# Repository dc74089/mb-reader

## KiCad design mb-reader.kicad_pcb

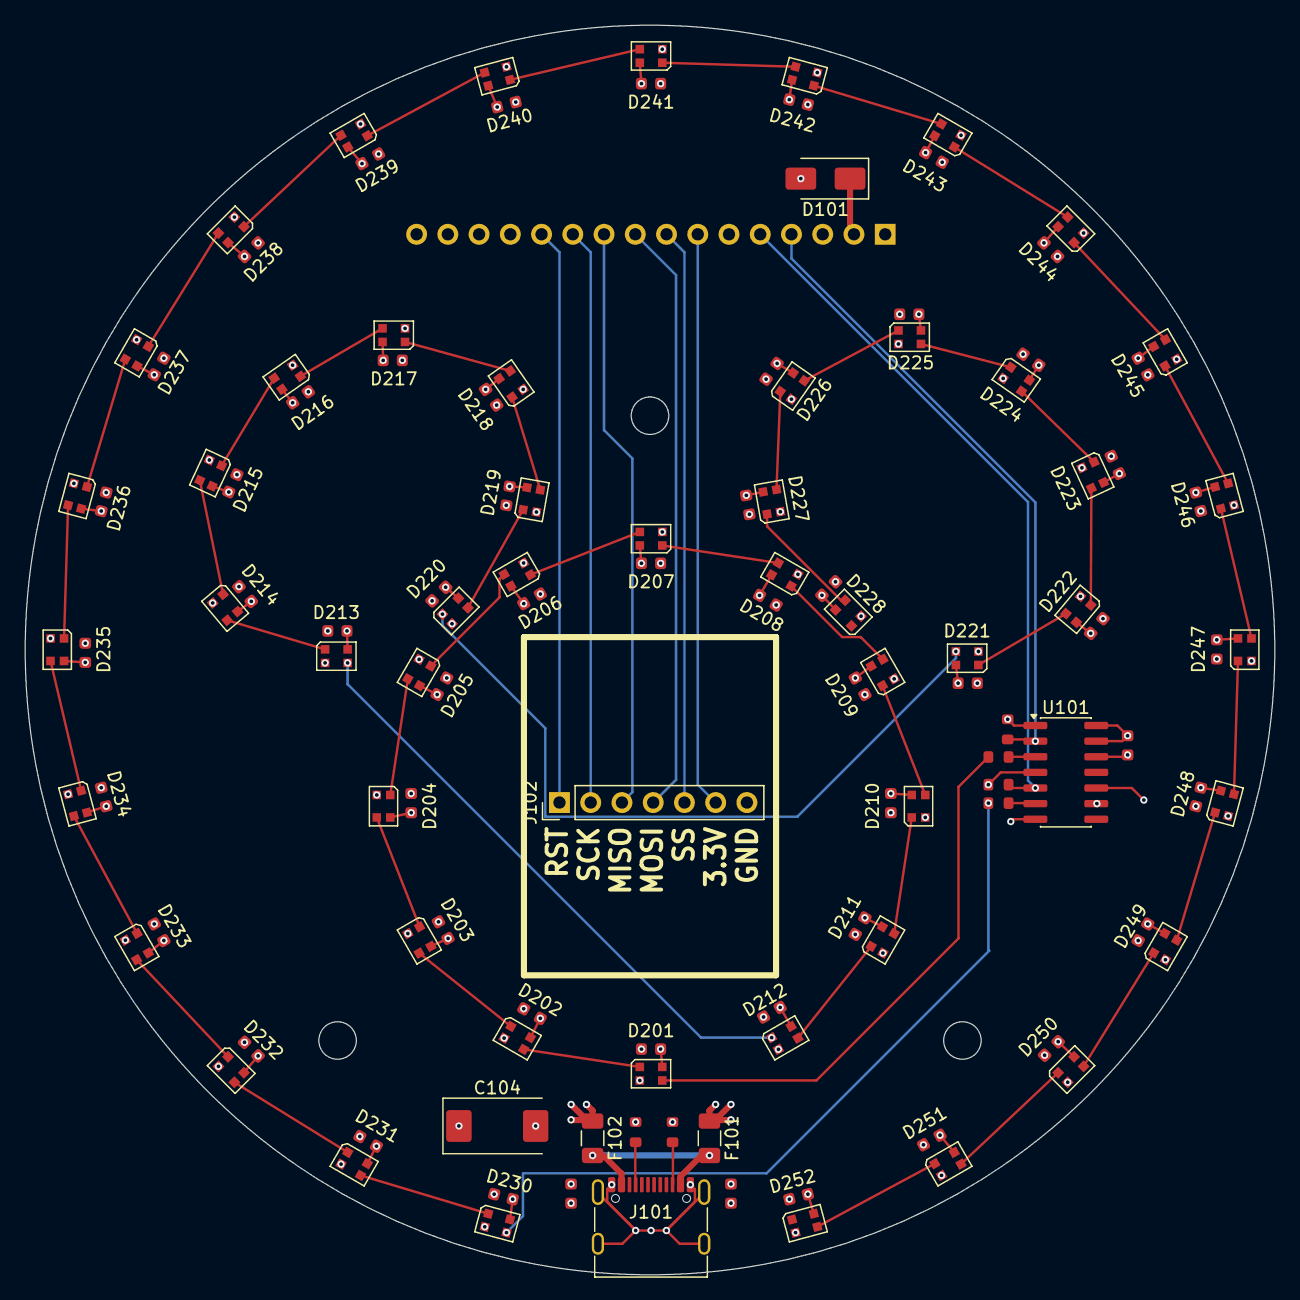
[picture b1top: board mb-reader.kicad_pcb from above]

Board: 4 copper layers, 101.6 x 101.6 mm, 119 parts (1 on the bottom side), 67 nets.

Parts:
C101, C103, C202, C203, C204, C205, C206, C207, C208, C209, C210, C211, C212, C213, C214, C215, C216, C217, C218, C219, C220, C221, C222, C223, C224, C225, C226, C227, C228, C229, C230, C231, C232, C233, C234, C235, C236, C237, C238, C239, C240, C241, C242, C243, C244, C245, C246, C247, C248, C249, C250, C251, C252: 100n; C_0603
C102: 10u; C_0603
C104: 100u; CP_EIA-7343-20_Kemet-V
D101: D; D_SMA
D201, D202, D203, D204, D205, D206, D207, D208, D209, D210, D211, D212, D213, D214, D215, D216, D217, D218, D219, D220, D221, D222, D223, D224, D225, D226, D227, D228, D230, D231, D232, D233, D234, D235, D236, D237, D238, D239, D240, D241, D242, D243, D244, D245, D246, D247, D248, D249, D250, D251, D252: WS2812B-2020; LED_WS2812B-2020_PLCC4_2.0x2.0mm
F101, F102: Polyfuse; Fuse_1206_3216Metric
J101: USB_C_Receptacle_USB2.0_14P; USB_C_Receptacle_G-Switch_GT-USB-7010ASV
J102: Conn_01x07_Socket; PinHeader_1x07_P2.54mm_Vertical
J103: Conn_01x16_Socket; PinHeader_1x16_P2.54mm_Vertical
R101, R102: 5k1; R_0603
R103, R104: 100; R_0603
R106, R107: 10k; R_0603
U101: 74AHCT125; SOIC-14_3.9x8.7mm_P1.27mm

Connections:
+3V3: J102.6, J103.7
+5V: C101.2, C102.2, C103.2, C104.1, C202.1, C203.1, C204.1, C205.1, C206.1, C207.1, C208.1, C209.1, C210.1, C211.1, C212.1, C213.1, C214.1, C215.1, C216.1, C217.1, C218.1, C219.1, C220.1, C221.1, C222.1, C223.1, C224.1, C225.1, C226.1, C227.1, C228.1, C229.1, C230.1, C231.1, C232.1, C233.1, C234.1, C235.1, C236.1, C237.1, C238.1, C239.1, C240.1, C241.1, C242.1, C243.1, C244.1, C245.1, C246.1, C247.1, C248.1, C249.1, C250.1, C251.1, C252.1, D101.2 (A), D201.4 (VDD), D202.4 (VDD), D203.4 (VDD), D204.4 (VDD), D205.4 (VDD), D206.4 (VDD), D207.4 (VDD), D208.4 (VDD), D209.4 (VDD), D210.4 (VDD), D211.4 (VDD), D212.4 (VDD), D213.4 (VDD), D214.4 (VDD), D215.4 (VDD), D216.4 (VDD), D217.4 (VDD), D218.4 (VDD), D219.4 (VDD), D220.4 (VDD), D221.4 (VDD), D222.4 (VDD), D223.4 (VDD), D224.4 (VDD), D225.4 (VDD), D226.4 (VDD), D227.4 (VDD), D228.4 (VDD), D230.4 (VDD), D231.4 (VDD), D232.4 (VDD), D233.4 (VDD), D234.4 (VDD), D235.4 (VDD), D236.4 (VDD), D237.4 (VDD), D238.4 (VDD), D239.4 (VDD), D240.4 (VDD), D241.4 (VDD), D242.4 (VDD), D243.4 (VDD), D244.4 (VDD), D245.4 (VDD), D246.4 (VDD), D247.4 (VDD), D248.4 (VDD), D249.4 (VDD), D250.4 (VDD), D251.4 (VDD), D252.4 (VDD), F101.1, F102.1, U101.10, U101.13, U101.14 (VCC)
/mb-reader/LED_1_3V: J103.4, R106.1, U101.2
/mb-reader/LED_2_3V: J103.5, R107.1, U101.5
/mb-reader/NFC_MISO: J102.3, J103.10
/mb-reader/NFC_MOSI: J102.4, J103.9
/mb-reader/NFC_RST: J102.1, J103.12
/mb-reader/NFC_SCK: J102.2, J103.11
/mb-reader/NFC_SS: J102.5, J103.8
/mb-reader/VBUS: F101.2, F102.2, J101.A4 (VBUS), J101.A9 (VBUS), J101.B4 (VBUS), J101.B9 (VBUS)
GND: C101.1, C102.1, C103.1, C104.2, C202.2, C203.2, C204.2, C205.2, C206.2, C207.2, C208.2, C209.2, C210.2, C211.2, C212.2, C213.2, C214.2, C215.2, C216.2, C217.2, C218.2, C219.2, C220.2, C221.2, C222.2, C223.2, C224.2, C225.2, C226.2, C227.2, C228.2, C229.2, C230.2, C231.2, C232.2, C233.2, C234.2, C235.2, C236.2, C237.2, C238.2, C239.2, C240.2, C241.2, C242.2, C243.2, C244.2, C245.2, C246.2, C247.2, C248.2, C249.2, C250.2, C251.2, C252.2, D201.2 (VSS), D202.2 (VSS), D203.2 (VSS), D204.2 (VSS), D205.2 (VSS), D206.2 (VSS), D207.2 (VSS), D208.2 (VSS), D209.2 (VSS), D210.2 (VSS), D211.2 (VSS), D212.2 (VSS), D213.2 (VSS), D214.2 (VSS), D215.2 (VSS), D216.2 (VSS), D217.2 (VSS), D218.2 (VSS), D219.2 (VSS), D220.2 (VSS), D221.2 (VSS), D222.2 (VSS), D223.2 (VSS), D224.2 (VSS), D225.2 (VSS), D226.2 (VSS), D227.2 (VSS), D228.2 (VSS), D230.2 (VSS), D231.2 (VSS), D232.2 (VSS), D233.2 (VSS), D234.2 (VSS), D235.2 (VSS), D236.2 (VSS), D237.2 (VSS), D238.2 (VSS), D239.2 (VSS), D240.2 (VSS), D241.2 (VSS), D242.2 (VSS), D243.2 (VSS), D244.2 (VSS), D245.2 (VSS), D246.2 (VSS), D247.2 (VSS), D248.2 (VSS), D249.2 (VSS), D250.2 (VSS), D251.2 (VSS), D252.2 (VSS), J101.A1 (GND), J101.A12 (GND), J101.B1 (GND), J101.B12 (GND), J101.SH (SHIELD), J102.7, J103.1, J103.3, J103.16, R101.1, R102.2, R106.2, R107.2, U101.1, U101.4, U101.7 (GND), U101.9, U101.12
LED_1: D201.3 (DIN), R103.2
LED_2: D230.3 (DIN), R104.2
unnamed: D101.1 (K), J103.2
unnamed: D201.1 (DOUT), D202.3 (DIN)
unnamed: D202.1 (DOUT), D203.3 (DIN)
unnamed: D203.1 (DOUT), D204.3 (DIN)
unnamed: D204.1 (DOUT), D205.3 (DIN)
unnamed: D205.1 (DOUT), D206.3 (DIN)
unnamed: D206.1 (DOUT), D207.3 (DIN)
unnamed: D207.1 (DOUT), D208.3 (DIN)
unnamed: D208.1 (DOUT), D209.3 (DIN)
unnamed: D209.1 (DOUT), D210.3 (DIN)
unnamed: D210.1 (DOUT), D211.3 (DIN)
unnamed: D211.1 (DOUT), D212.3 (DIN)
unnamed: D212.1 (DOUT), D213.3 (DIN)
unnamed: D213.1 (DOUT), D214.3 (DIN)
unnamed: D214.1 (DOUT), D215.3 (DIN)
unnamed: D215.1 (DOUT), D216.3 (DIN)
unnamed: D216.1 (DOUT), D217.3 (DIN)
unnamed: D217.1 (DOUT), D218.3 (DIN)
unnamed: D218.1 (DOUT), D219.3 (DIN)
unnamed: D219.1 (DOUT), D220.3 (DIN)
unnamed: D220.1 (DOUT), D221.3 (DIN)
unnamed: D221.1 (DOUT), D222.3 (DIN)
unnamed: D222.1 (DOUT), D223.3 (DIN)
unnamed: D223.1 (DOUT), D224.3 (DIN)
unnamed: D224.1 (DOUT), D225.3 (DIN)
unnamed: D225.1 (DOUT), D226.3 (DIN)
unnamed: D226.1 (DOUT), D227.3 (DIN)
unnamed: D227.1 (DOUT), D228.3 (DIN)
unnamed: D230.1 (DOUT), D231.3 (DIN)
unnamed: D231.1 (DOUT), D232.3 (DIN)
unnamed: D232.1 (DOUT), D233.3 (DIN)
unnamed: D233.1 (DOUT), D234.3 (DIN)
unnamed: D234.1 (DOUT), D235.3 (DIN)
unnamed: D235.1 (DOUT), D236.3 (DIN)
unnamed: D236.1 (DOUT), D237.3 (DIN)
unnamed: D237.1 (DOUT), D238.3 (DIN)
unnamed: D238.1 (DOUT), D239.3 (DIN)
unnamed: D239.1 (DOUT), D240.3 (DIN)
unnamed: D240.1 (DOUT), D241.3 (DIN)
unnamed: D241.1 (DOUT), D242.3 (DIN)
unnamed: D242.1 (DOUT), D243.3 (DIN)
unnamed: D243.1 (DOUT), D244.3 (DIN)
unnamed: D244.1 (DOUT), D245.3 (DIN)
unnamed: D245.1 (DOUT), D246.3 (DIN)
unnamed: D246.1 (DOUT), D247.3 (DIN)
unnamed: D247.1 (DOUT), D248.3 (DIN)
unnamed: D248.1 (DOUT), D249.3 (DIN)
unnamed: D249.1 (DOUT), D250.3 (DIN)
unnamed: D250.1 (DOUT), D251.3 (DIN)
unnamed: D251.1 (DOUT), D252.3 (DIN)
unnamed: J101.A5 (CC1), R101.2
unnamed: J101.B5 (CC2), R102.1
unnamed: R103.1, U101.3
unnamed: R104.1, U101.6

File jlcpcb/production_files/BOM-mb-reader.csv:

Comment,Designator,Footprint,LCSC,Quantity
100,"R103,R104",R_0603,C22775,2
100n,"C101,C103,C202,C203,C204,C205,C206,C207,C208,C209,C210,C211,C212,C213,C214,C215,C216,C217,C218,C219,C220,C221,C222,C223,C224,C225,C226,C227,C228,C229,C230,C231,C232,C233,C234,C235,C236,C237,C238,C239,C240,C241,C242,C243,C244,C245,C246,C247,C248,C249,C250,C251,C252",C_0603,C14663,53
100u,C104,CP_EIA-7343-20_Kemet-V,C219004,1
10k,"R106,R107",R_0603,C23192,2
10u,C102,C_0603,C96446,1
5k1,"R101,R102",R_0603,C23186,2
74AHCT125,U101,SOIC-14_3.9x8.7mm_P1.27mm,C155176,1
D,D101,D_SMA,C8678,1
Polyfuse,"F101,F102",Fuse_1206_3216Metric,C126818,2
USB_C_Receptacle_USB2.0_14P,J101,USB_C_Receptacle_G-Switch_GT-USB-7010ASV,C2988369,1
WS2812B-2020,"D201,D202,D203,D204,D205,D206,D207,D208,D209,D210,D211,D212,D213,D214,D215,D216,D217,D218,D219,D220,D221,D222,D223,D224,D225,D226,D227,D228,D230,D231,D232,D233,D234,D235,D236,D237,D238,D239,D240,D241,D242,D243,D244,D245,D246,D247,D248,D249,D250,D251,D252",LED_WS2812B-2020_PLCC4_2.0x2.0mm,C52917434,51
